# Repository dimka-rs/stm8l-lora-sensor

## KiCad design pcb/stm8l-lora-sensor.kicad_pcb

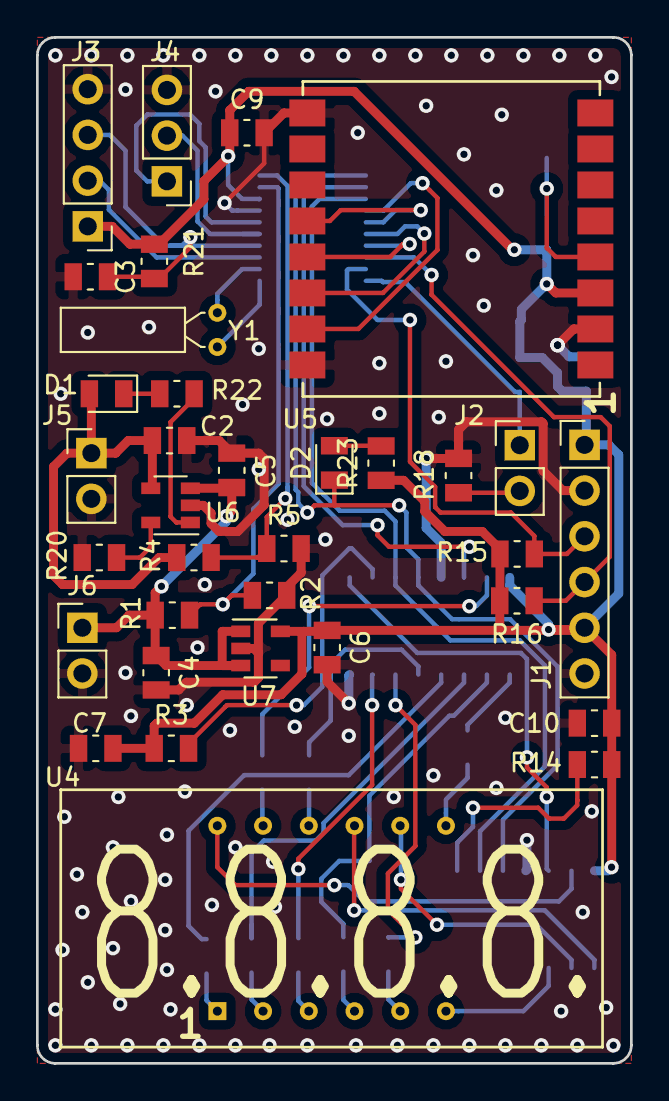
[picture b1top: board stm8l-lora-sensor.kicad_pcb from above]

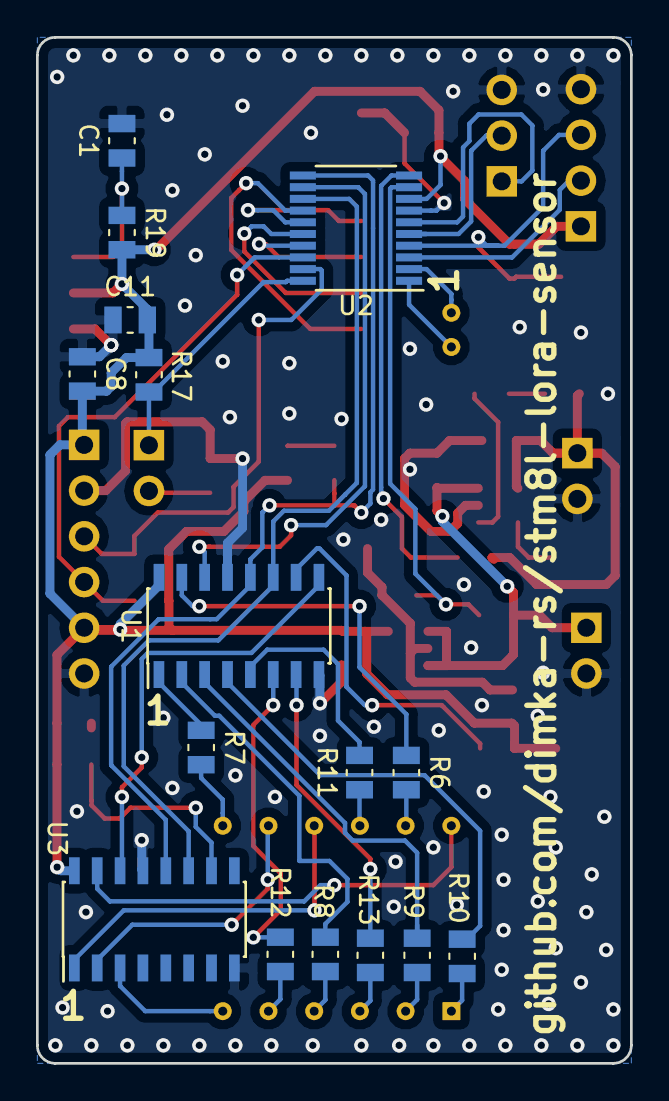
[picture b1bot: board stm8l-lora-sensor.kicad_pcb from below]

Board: 2 copper layers, 33.0 x 57.0 mm, 50 parts (16 on the bottom side), 51 nets.

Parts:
C1, C3, C7, C8, C9, C10, C11: 0.1u; C_0805_2012Metric
C2, C5: 4.7u; C_0805_2012Metric
C4, C6: 1u; C_0805_2012Metric
D1, D2: LED; LED_0805_2012Metric
J1: Conn_01x06; PinHeader_1x06_P2.54mm_Vertical
J2, J5, J6: Conn_01x02; PinHeader_1x02_P2.54mm_Vertical
J3: Conn_01x04; PinHeader_1x04_P2.54mm_Vertical
J4: Conn_01x03; PinHeader_1x03_P2.54mm_Vertical
R1, R2, R4, R5, R17: 100k; R_0805_2012Metric
R3, R14, R15, R16, R19, R20, R21: 10k; R_0805_2012Metric
R6, R7, R8, R9, R10, R11, R12, R13, R18, R23: 1k; R_0805_2012Metric
R22: 470; R_0805_2012Metric
U1, U3: 74HC595; SOIC-16_3.9x9.9mm_P1.27mm
U2: STM8L051F3P; TSSOP-20_4.4x6.5mm_P0.65mm
U4: HX3641BH
U5: Ai-Thinker-Ra-01; Ai-Thinker-Ra-01-LoRa
U6: MCP73831-2-OT; SOT-23-5
U7: LP2985-3.3; SOT-23-5
Y1: Crystal; Crystal_C26-LF_D2.1mm_L6.5mm_Horizontal

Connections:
+5V: C2.1, D1.2, J5.1, R4.1, U6.4
+BATT: C4.1, C5.1, J6.1, R1.1, U6.3, U7.1, U7.3
ADC_LIPO: R1.2, R2.1, U2.9
ADC_SOLAR: R4.2, R5.1, U2.10
BTN: J2.1, R17.1, U2.20
CS_LORA: U2.14, U5.15
DRX: J4.1, U2.6
DTX: J4.2, U2.5
GND: C1.2, C2.2, C3.2, C4.2, C5.2, C6.2, C7.2, C8.1, C9.2, C10.2, C11.1, J1.2, J1.6, J3.4, J4.3, J5.2, J6.2, R2.2, R5.2, R18.1, R20.1, U1.8, U1.13, U2.7, U3.8, U3.13, U5.2, U5.9, U5.16, U6.2, U7.2
IND_CLK: U1.11, U2.13, U3.11
IND_DATA: U1.14, U2.12
IND_LATCH: D2.1, U1.12, U2.11, U3.12
unnamed: C1.1, R19.1, U5.4
unnamed: D1.1, R22.1
unnamed: D2.2, R23.2
unnamed: J2.2, R18.2
unnamed: R3.2, U1.10
unnamed: R6.1, U1.15
unnamed: R6.2, U4.11
unnamed: R7.1, U1.1
unnamed: R7.2, U4.7
unnamed: R8.1, U1.2
unnamed: R8.2, U4.4
unnamed: R9.1, U1.3
unnamed: R9.2, U4.2
unnamed: R10.1, U1.4
unnamed: R10.2, U4.1
unnamed: R11.1, U1.5
unnamed: R11.2, U4.10
unnamed: R12.1, U1.6
unnamed: R12.2, U4.5
unnamed: R13.1, U1.7
unnamed: R13.2, U4.3
unnamed: R14.2, U3.10
unnamed: R20.2, U6.5
unnamed: R22.2, U6.1
unnamed: U1.9, U3.14
unnamed: U2.1, Y1.2
unnamed: U2.2, Y1.1
unnamed: U3.1, U4.9
unnamed: U3.2, U4.8
unnamed: U3.3, U4.6
unnamed: U3.15, U4.12
RST: C3.1, J3.3, R21.1, U2.4
SCL: J1.3, R15.1, U2.19
SDA: J1.4, R16.1, U2.18
SPI1_MISO: U2.17, U5.13
SPI1_MOSI: U2.16, U5.14
SPI1_SCK: U2.15, U5.12
SWIM: J3.2, U2.3
VCC: C6.1, C7.1, C8.2, C9.1, C10.1, C11.2, J1.1, J1.5, J3.1, R3.1, R14.1, R15.2, R16.2, R17.2, R19.2, R21.2, R23.1, U1.16, U2.8, U3.16, U5.3, U7.5

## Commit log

2018-03-21 added device block diagram
2018-03-21 replace svg diagram with png
2018-03-21 forgot image
2018-03-21 forgot change readme
2018-03-21 Sensor over spi, sch draft
2018-03-21 pcb draft
2018-03-26 sch done, but requires rethink
2018-03-26 sensor back on i2c
2018-03-27 pcb placement done. Have to change LED indicator
2018-03-27 pwr flags added
2018-03-28 Added bypass caps, started pcb
2018-03-28 more pcb
2018-03-29 LED IND replaced, pcb almost ready
2018-03-30 pcb done
2018-03-30 updated device block diagram
2018-03-31 added activity indicator for sensor node
2018-03-31 pcb update
2018-03-31 pcb: rounded squares
2018-03-31 pcb: added url
